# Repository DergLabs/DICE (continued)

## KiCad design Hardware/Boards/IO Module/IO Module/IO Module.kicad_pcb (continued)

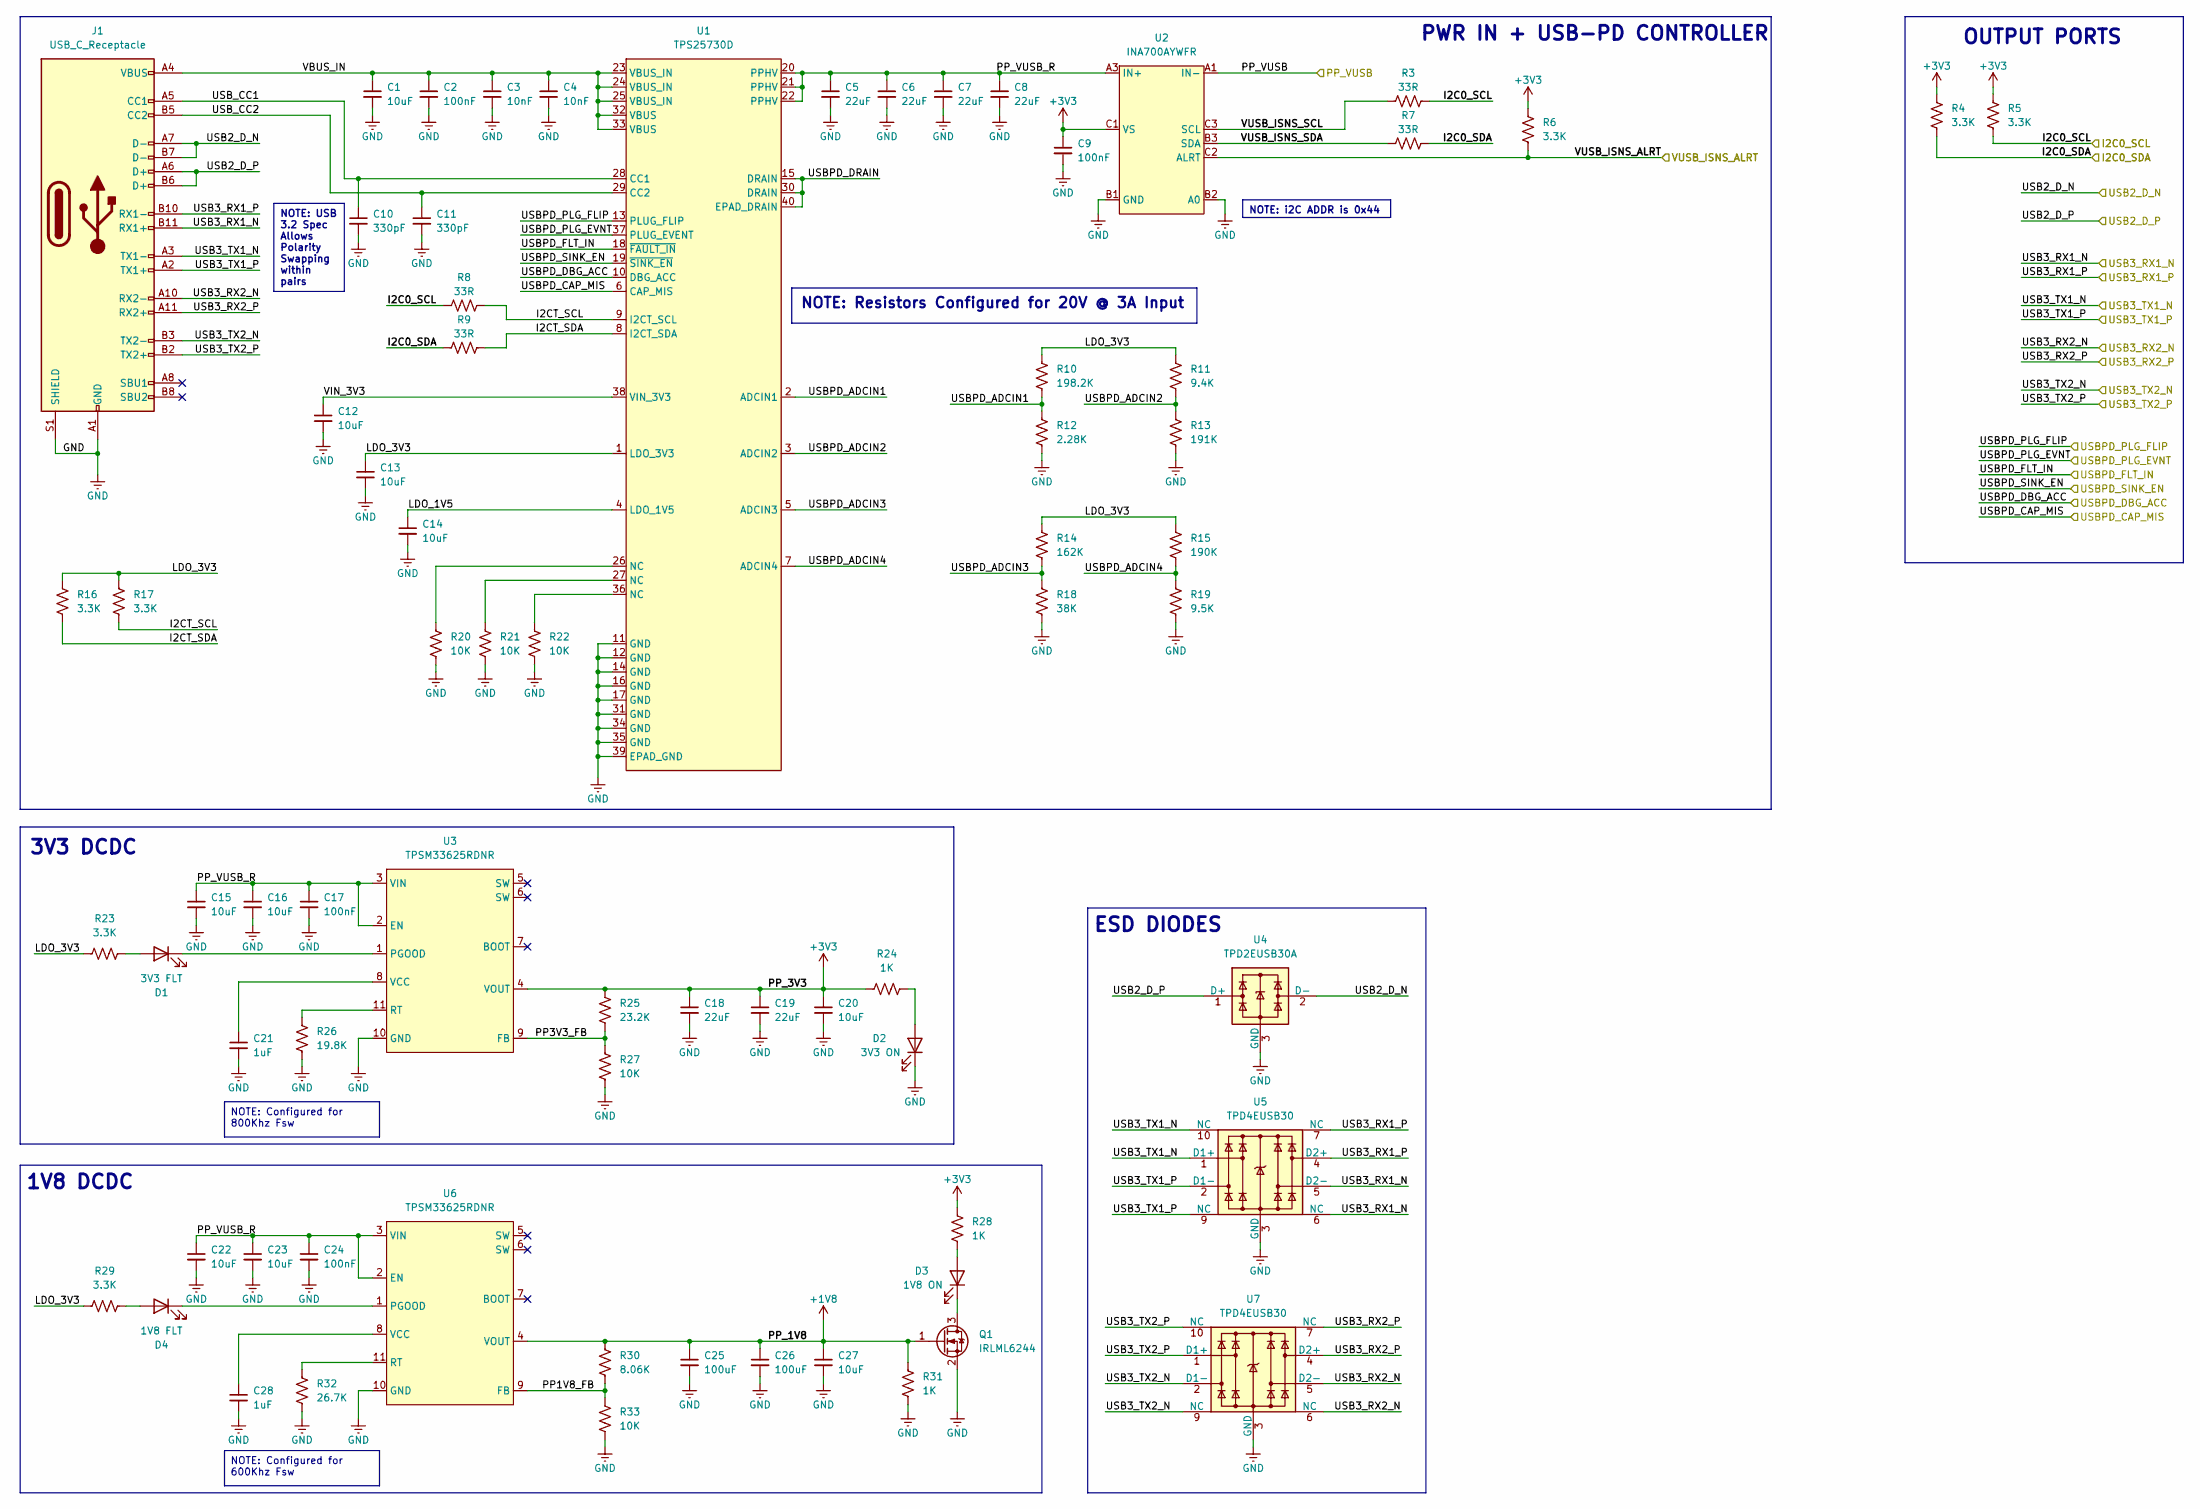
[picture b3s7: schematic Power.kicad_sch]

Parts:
C1, C12, C13, C14, C15, C16, C20, C22, C23, C27: 10uF; C_0603_1608Metric
C2, C9, C17, C24: 100nF; C_0201_0603Metric
C3, C4: 10nF; C_0201_0603Metric
C5, C6, C7, C8, C18, C19: 22uF; C_0805_2012Metric
C10, C11: 330pF; C_0201_0603Metric
C21, C28: 1uF; C_0201_0603Metric
C25, C26: 100uF; C_0805_2012Metric
D1: 3V3 FLT; LED_0603_1608Metric
D2: 3V3 ON; LED_0603_1608Metric
D3: 1V8 ON; LED_0603_1608Metric
D4: 1V8 FLT; LED_0603_1608Metric
J1: USB_C_Receptacle; GCT_USB4056-03-A_REVA2
Q1: IRLML6244; SOT-23
R3, R7, R8, R9: 33R; R_0201_0603Metric
R4, R5, R6, R16, R17, R23, R29: 3.3K; R_0201_0603Metric
R10: 198.2K; R_0201_0603Metric
R11: 9.4K; R_0201_0603Metric
R12: 2.28K; R_0201_0603Metric
R13: 191K; R_0201_0603Metric
R14: 162K; R_0201_0603Metric
R15: 190K; R_0201_0603Metric
R18: 38K; R_0201_0603Metric
R19: 9.5K; R_0201_0603Metric
R20, R21, R22, R27, R33: 10K; R_0201_0603Metric
R24, R28, R31: 1K; R_0201_0603Metric
R25: 23.2K; R_0201_0603Metric
R26: 19.8K; R_0201_0603Metric
R30: 8.06K; R_0201_0603Metric
R32: 26.7K; R_0201_0603Metric
U1: TPS25730D; TPS25730DREFR
U2: INA700AYWFR; INA700_AYWFR
U3, U6: TPSM33625RDNR; RDN0011A-MFG
U4: TPD2EUSB30A; Texas_DRT-3
U5, U7: TPD4EUSB30; USON-10_2.5x1.0mm_P0.5mm

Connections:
+1V8: C25.1, C26.1, C27.1, Q1.1 (G), R30.2, R31.2, U6.4 (VOUT); also elsewhere on the board
+3V3: C9.1, C18.1, C19.1, C20.1, R4.2, R5.2, R6.2, R24.1, R25.2, R28.2, U2.C1 (VS), U3.4 (VOUT); also elsewhere on the board
/Top/MCU/I2C0_SCL: R3.1, R5.1, R8.2; also elsewhere on the board
/Top/MCU/I2C0_SDA: R4.1, R7.1, R9.2; also elsewhere on the board
/Top/MCU/USBPD_CAP_MIS: U1.6 (CAP_MIS); also elsewhere on the board
/Top/MCU/USBPD_DBG_ACC: U1.10 (DBG_ACC); also elsewhere on the board
/Top/MCU/USBPD_FLT_IN: U1.18 (~FAULT_IN); also elsewhere on the board
/Top/MCU/USBPD_PLG_EVNT: U1.37 (PLUG_EVENT); also elsewhere on the board
/Top/MCU/USBPD_PLG_FLIP: U1.13 (PLUG_FLIP); also elsewhere on the board
/Top/MCU/USBPD_SINK_EN: U1.19 (~SINK_EN); also elsewhere on the board
/Top/MCU/VUSB_ISNS_ALRT: R6.1, U2.C2 (ALRT); also elsewhere on the board
/Top/PP_VUSB: U2.A1 (IN-); also elsewhere on the board
/Top/Power/I2CT_SCL: R8.1, R17.1, U1.9 (I2CT_SCL)
/Top/Power/I2CT_SDA: R9.1, R16.1, U1.8 (I2CT_SDA)
/Top/Power/LDO_1V5: C14.1, U1.4 (LDO_1V5)
/Top/Power/LDO_3V3: C13.1, R10.2, R11.2, R14.2, R15.2, R16.2, R17.2, R23.1, R29.1, U1.1 (LDO_3V3)
/Top/Power/PP1V8_FB: R30.1, R33.2, U6.9 (FB)
/Top/Power/PP3V3_FB: R25.1, R27.2, U3.9 (FB)
/Top/Power/PP_VUSB_R: C5.1, C6.1, C7.1, C8.1, C15.1, C16.1, C17.1, C22.1, C23.1, C24.1, U1.20 (PPHV), U1.21 (PPHV), U1.22 (PPHV), U2.A3 (IN+), U3.2 (EN), U3.3 (VIN), U6.2 (EN), U6.3 (VIN)
/Top/Power/USB2_D_N: J1.A7 (D-), J1.B7 (D-), U4.2 (D-); also elsewhere on the board
/Top/Power/USB2_D_P: J1.A6 (D+), J1.B6 (D+), U4.1 (D+); also elsewhere on the board
/Top/Power/USB3_RX1_N: J1.B11 (RX1+), U5.5 (D2-), U5.6 (NC); also elsewhere on the board
/Top/Power/USB3_RX1_P: J1.B10 (RX1-), U5.4 (D2+), U5.7 (NC); also elsewhere on the board
/Top/Power/USB3_RX2_N: J1.A10 (RX2-), U7.5 (D2-), U7.6 (NC); also elsewhere on the board
/Top/Power/USB3_RX2_P: J1.A11 (RX2+), U7.4 (D2+), U7.7 (NC); also elsewhere on the board
/Top/Power/USB3_TX1_N: J1.A3 (TX1-), U5.1 (D1+), U5.10 (NC); also elsewhere on the board
/Top/Power/USB3_TX1_P: J1.A2 (TX1+), U5.2 (D1-), U5.9 (NC); also elsewhere on the board
/Top/Power/USB3_TX2_N: J1.B3 (TX2-), U7.2 (D1-), U7.9 (NC); also elsewhere on the board
/Top/Power/USB3_TX2_P: J1.B2 (TX2+), U7.1 (D1+), U7.10 (NC); also elsewhere on the board
/Top/Power/USBPD_ADCIN1: R10.1, R12.2, U1.2 (ADCIN1)
/Top/Power/USBPD_ADCIN2: R11.1, R13.2, U1.3 (ADCIN2)
/Top/Power/USBPD_ADCIN3: R14.1, R18.2, U1.5 (ADCIN3)
/Top/Power/USBPD_ADCIN4: R15.1, R19.2, U1.7 (ADCIN4)
/Top/Power/USBPD_DRAIN: U1.15 (DRAIN), U1.30 (DRAIN), U1.40 (EPAD_DRAIN)
/Top/Power/USB_CC1: C10.1, J1.A5 (CC1), U1.28 (CC1)
/Top/Power/USB_CC2: C11.1, J1.B5 (CC2), U1.29 (CC2)
/Top/Power/VBUS_IN: C1.1, C2.1, C3.1, C4.1, J1.A4 (VBUS), J1.A9 (VBUS), J1.B4 (VBUS), J1.B9 (VBUS), U1.23 (VBUS_IN), U1.24 (VBUS_IN), U1.25 (VBUS_IN), U1.32 (VBUS), U1.33 (VBUS)
/Top/Power/VIN_3V3: C12.1, U1.38 (VIN_3V3)
/Top/Power/VUSB_ISNS_SCL: R3.2, U2.C3 (SCL)
/Top/Power/VUSB_ISNS_SDA: R7.2, U2.B3 (SDA)
GND: C1.2, C2.2, C3.2, C4.2, C5.2, C6.2, C7.2, C8.2, C9.2, C10.2, C11.2, C12.2, C13.2, C14.2, C15.2, C16.2, C17.2, C18.2, C19.2, C20.2, C21.2, C22.2, C23.2, C24.2, C25.2, C26.2, C27.2, C28.2, D2.1 (K), J1.A1 (GND), J1.A12 (GND), J1.B1 (GND), J1.B12 (GND), J1.S1 (SHIELD), Q1.2 (S), R12.1, R13.1, R18.1, R19.1, R20.1, R21.1, R22.1, R26.1, R27.1, R31.1, R32.1, R33.1, U1.11 (GND), U1.12 (GND), U1.14 (GND), U1.16 (GND), U1.17 (GND), U1.31 (GND), U1.34 (GND), U1.35 (GND), U1.39 (EPAD_GND), U2.B1 (GND), U2.B2 (A0), U3.10 (GND), U4.3 (GND), U5.3 (GND), U5.8 (GND), U6.10 (GND), U7.3 (GND), U7.8 (GND); also elsewhere on the board
unnamed: D1.2 (A), R23.2
unnamed: D1.1 (K), U3.1 (PGOOD)
unnamed: D2.2 (A), R24.2
unnamed: D3.2 (A), R28.1
unnamed: D3.1 (K), Q1.3 (D)
unnamed: D4.2 (A), R29.2
unnamed: D4.1 (K), U6.1 (PGOOD)
unnamed: R20.2, U1.26 (NC)
unnamed: R21.2, U1.27 (NC)
unnamed: R22.2, U1.36 (NC)
unnamed: R26.2, U3.11 (RT)
unnamed: C21.1, U3.8 (VCC)
unnamed: R32.2, U6.11 (RT)
unnamed: C28.1, U6.8 (VCC)

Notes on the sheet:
NOTE: Configured for 800Khz Fsw
NOTE: Resistors Configured for 20V @ 3A Input
NOTE: Configured for 600Khz Fsw
NOTE: USB 3.2 Spec Allows Polarity Swapping within pairs
NOTE: i2C ADDR is 0x44
PWR IN + USB-PD CONTROLLER
OUTPUT PORTS
1V8 DCDC
3V3 DCDC
ESD DIODES

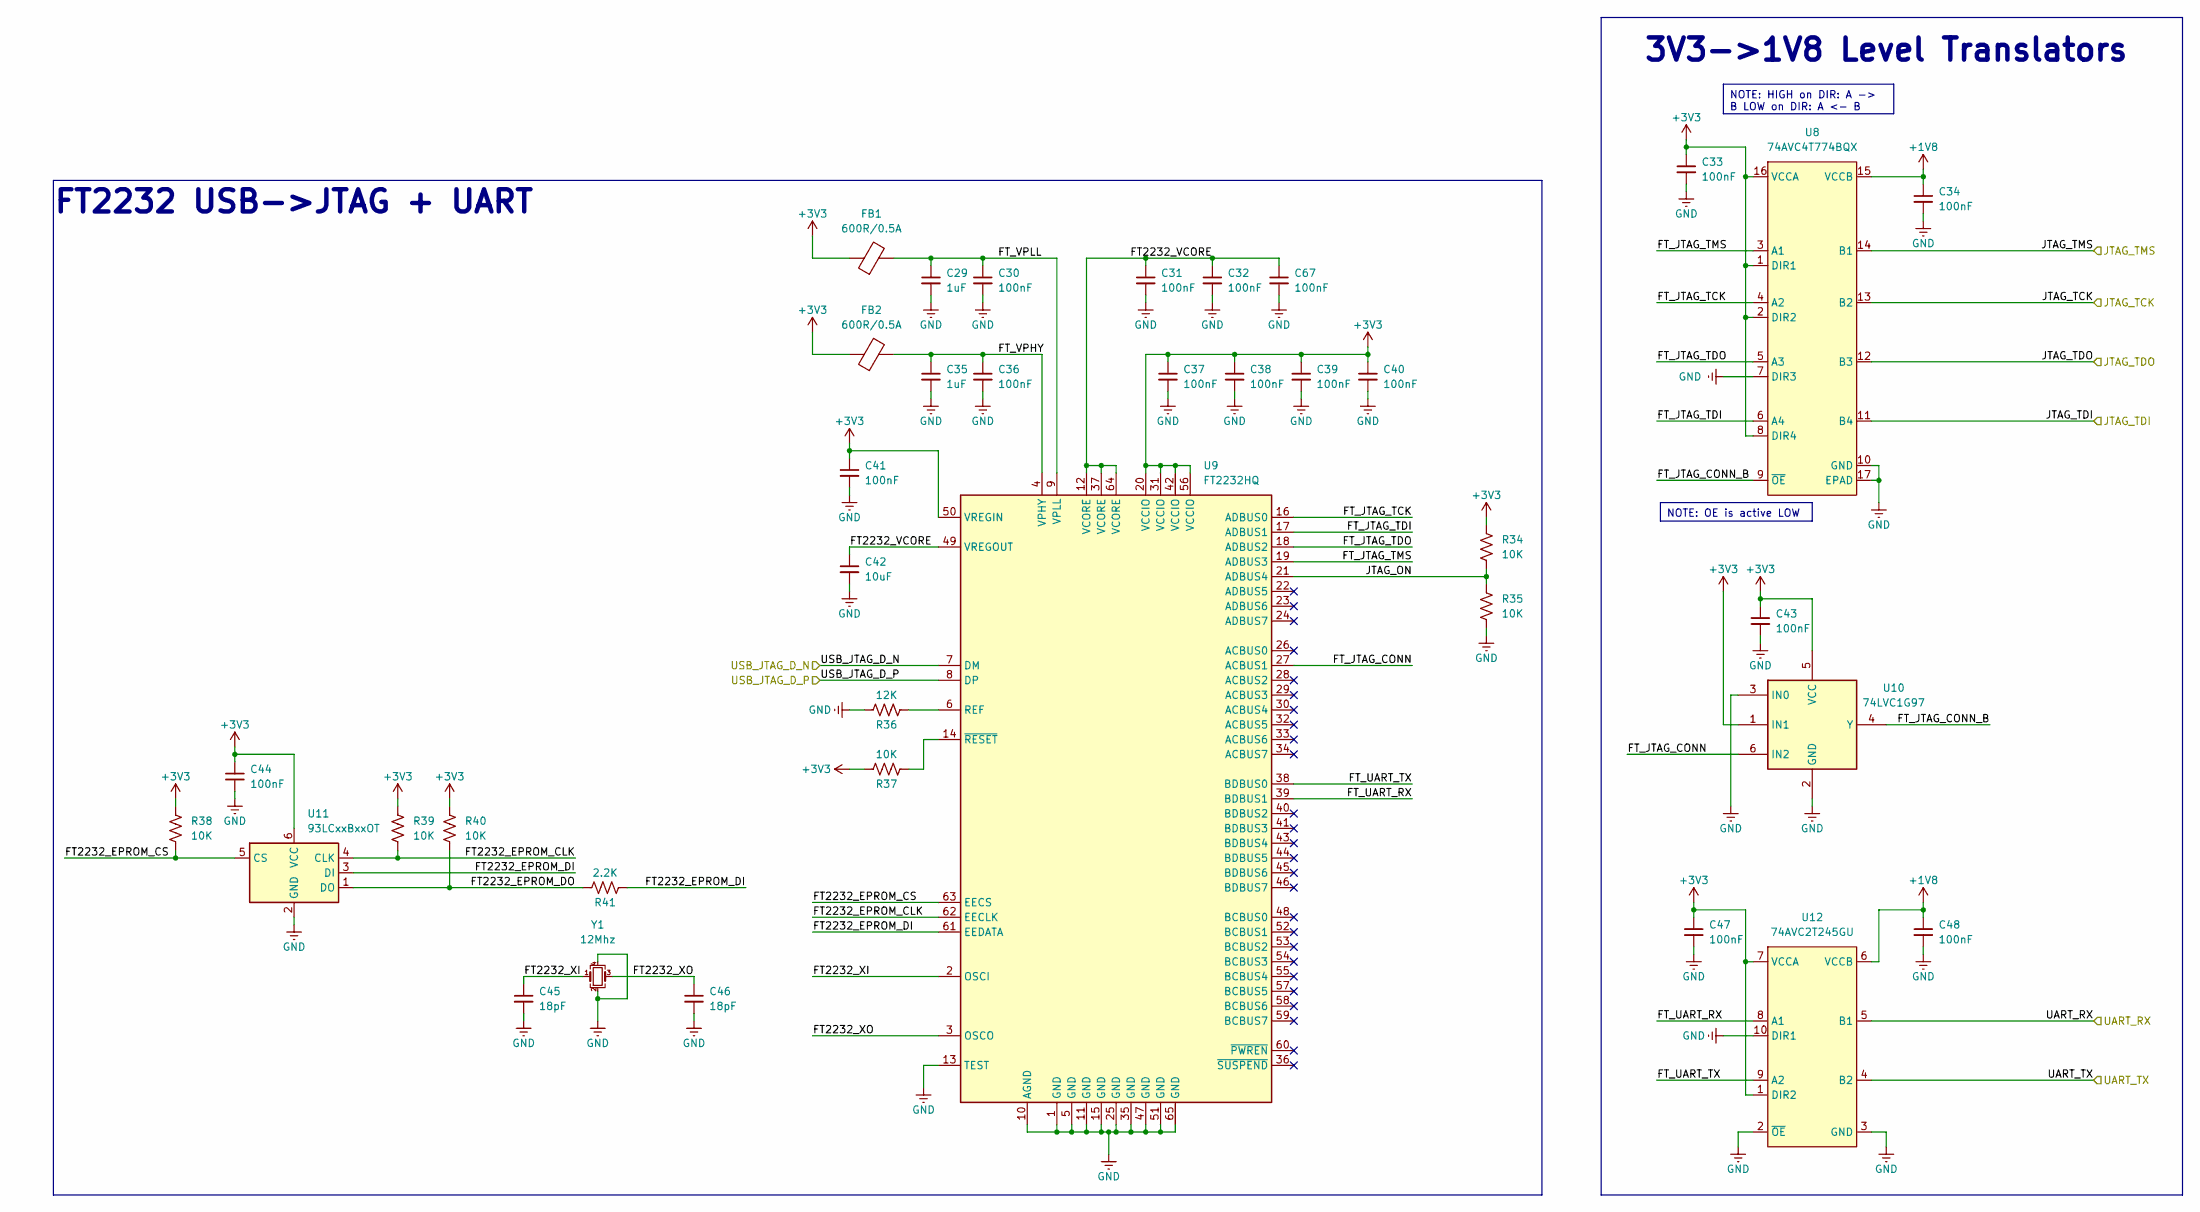
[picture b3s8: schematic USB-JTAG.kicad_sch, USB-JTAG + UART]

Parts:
C29, C35: 1uF; C_0201_0603Metric
C30, C31, C32, C33, C34, C36, C37, C38, C39, C40, C41, C43, C44, C47, C48, C67: 100nF; C_0201_0603Metric
C42: 10uF; C_0603_1608Metric
C45, C46: 18pF; C_0201_0603Metric
FB1, FB2: 600R/0.5A; L_0603_1608Metric
R34, R35, R37, R38, R39, R40: 10K; R_0201_0603Metric
R36: 12K; R_0201_0603Metric
R41: 2.2K; R_0201_0603Metric
U8: 74AVC4T774BQX
U9: FT2232HQ; QFN-64-1EP_9x9mm_P0.5mm_EP4.35x4.35mm
U10: 74LVC1G97; SOT-563
U11: 93LCxxBxxOT; SOT-23-6
U12: 74AVC2T245GU
Y1: 12Mhz; Oscillator_SMD_Abracon_ASE-4Pin_3.2x2.5mm

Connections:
+1V8: C34.1, C48.1, U8.15 (VCCB), U12.6 (VCCB); also elsewhere on the board
+3V3: C33.1, C37.1, C38.1, C39.1, C40.1, C41.1, C43.1, C44.1, C47.1, FB1.1, FB2.1, R34.2, R37.2, R38.2, R39.2, R40.2, U8.1 (DIR1), U8.2 (DIR2), U8.8 (DIR4), U8.16 (VCCA), U9.20 (VCCIO), U9.31 (VCCIO), U9.42 (VCCIO), U9.50 (VREGIN), U9.56 (VCCIO), U10.1 (IN1), U10.5 (VCC), U11.6 (VCC), U12.1 (DIR2), U12.7 (VCCA); also elsewhere on the board
/Top/B2B/JTAG_TCK: U8.13 (B2); also elsewhere on the board
/Top/B2B/JTAG_TDI: U8.11 (B4); also elsewhere on the board
/Top/B2B/JTAG_TDO: U8.12 (B3); also elsewhere on the board
/Top/B2B/JTAG_TMS: U8.14 (B1); also elsewhere on the board
/Top/B2B/UART_RX: U12.5 (B1); also elsewhere on the board
/Top/B2B/UART_TX: U12.4 (B2); also elsewhere on the board
/Top/USB Hub/USB_JTAG_D_N: U9.7 (DM); also elsewhere on the board
/Top/USB Hub/USB_JTAG_D_P: U9.8 (DP); also elsewhere on the board
/Top/USB-JTAG/FT2232_EPROM_CLK: R39.1, U9.62 (EECLK), U11.4 (CLK)
/Top/USB-JTAG/FT2232_EPROM_CS: R38.1, U9.63 (EECS), U11.5 (CS)
/Top/USB-JTAG/FT2232_EPROM_DI: R41.1, U9.61 (EEDATA), U11.3 (DI)
/Top/USB-JTAG/FT2232_EPROM_DO: R40.1, R41.2, U11.1 (DO)
/Top/USB-JTAG/FT2232_VCORE: C31.1, C32.1, C42.1, C67.1, U9.12 (VCORE), U9.37 (VCORE), U9.49 (VREGOUT), U9.64 (VCORE)
/Top/USB-JTAG/FT2232_XI: C45.1, U9.2 (OSCI), Y1.1
/Top/USB-JTAG/FT2232_XO: C46.1, U9.3 (OSCO), Y1.3
/Top/USB-JTAG/FT_JTAG_CONN: U9.27 (ACBUS1), U10.6 (IN2)
/Top/USB-JTAG/FT_JTAG_CONN_B: U8.9 (~OE), U10.4 (Y)
/Top/USB-JTAG/FT_JTAG_TCK: U8.4 (A2), U9.16 (ADBUS0)
/Top/USB-JTAG/FT_JTAG_TDI: U8.6 (A4), U9.17 (ADBUS1)
/Top/USB-JTAG/FT_JTAG_TDO: U8.5 (A3), U9.18 (ADBUS2)
/Top/USB-JTAG/FT_JTAG_TMS: U8.3 (A1), U9.19 (ADBUS3)
/Top/USB-JTAG/FT_UART_RX: U9.39 (BDBUS1), U12.8 (A1)
/Top/USB-JTAG/FT_UART_TX: U9.38 (BDBUS0), U12.9 (A2)
/Top/USB-JTAG/FT_VPHY: C35.1, C36.1, FB2.2, U9.4 (VPHY)
/Top/USB-JTAG/FT_VPLL: C29.1, C30.1, FB1.2, U9.9 (VPLL)
/Top/USB-JTAG/JTAG_ON: R34.1, R35.2, U9.21 (ADBUS4)
GND: C29.2, C30.2, C31.2, C32.2, C33.2, C34.2, C35.2, C36.2, C37.2, C38.2, C39.2, C40.2, C41.2, C42.2, C43.2, C44.2, C45.2, C46.2, C47.2, C48.2, C67.2, R35.1, R36.2, U8.7 (DIR3), U8.10 (GND), U8.17 (EPAD), U9.1 (GND), U9.5 (GND), U9.10 (AGND), U9.11 (GND), U9.13 (TEST), U9.15 (GND), U9.25 (GND), U9.35 (GND), U9.47 (GND), U9.51 (GND), U9.65 (GND), U10.2 (GND), U10.3 (IN0), U11.2 (GND), U12.2 (~OE), U12.3 (GND), U12.10 (DIR1), Y1.2, Y1.4; also elsewhere on the board
unnamed: R36.1, U9.6 (REF)
unnamed: R37.1, U9.14 (~RESET)

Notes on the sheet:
NOTE: OE is active LOW
NOTE: HIGH on DIR: A -> B LOW on DIR: A <- B
FT2232 USB->JTAG + UART
3V3->1V8 Level Translators

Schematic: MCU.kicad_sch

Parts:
C50, C69, C70, C71, C72, C74, C75, C76: 100nF; C_0201_0603Metric
C68, C73: 1uF; C_0201_0603Metric
C77, C78: 18pF; C_0201_0603Metric
D5: MCU Heartbeat; LED_0603_1608Metric
R47: 10K; R_0201_0603Metric; MPN RC0402JR-0710KL
R48: 1K; R_0201_0603Metric
SW1: RST; SW_Push_SPST_NO_Alps_SKRK
TP5, TP6: TestPoint; TestPoint_Pad_D1.0mm
U14: W25Q16JVUXIQ TR; USON-8_UX_2x3x0p6_WIN
U15: RP2040; QFN-56-1EP_7x7mm_P0.4mm_EP3.2x3.2mm
Y3: 12Mhz; Oscillator_SMD_Abracon_ASE-4Pin_3.2x2.5mm

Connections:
+3V3: C70.1, C71.1, C72.1, C73.1, C74.1, C75.1, C76.1, U14.8 (VCC), U15.1 (IOVDD), U15.10 (IOVDD), U15.22 (IOVDD), U15.33 (IOVDD), U15.42 (IOVDD), U15.43 (ADC_AVDD), U15.44 (VREG_IN), U15.48 (USB_VDD), U15.49 (IOVDD); also elsewhere on the board
/Top/B2B/CAM_LED_EN: U15.5 (GPIO3); also elsewhere on the board
/Top/B2B/CAM_PWR_EN: U15.4 (GPIO2); also elsewhere on the board
/Top/B2B/MBUS_D0: U15.11 (GPIO8); also elsewhere on the board
/Top/B2B/MBUS_D1: U15.12 (GPIO9); also elsewhere on the board
/Top/B2B/MBUS_D2: U15.13 (GPIO10); also elsewhere on the board
/Top/B2B/MBUS_D3: U15.14 (GPIO11); also elsewhere on the board
/Top/B2B/MBUS_D4: U15.15 (GPIO12); also elsewhere on the board
/Top/B2B/MBUS_D5: U15.16 (GPIO13); also elsewhere on the board
/Top/B2B/MBUS_D6: U15.17 (GPIO14); also elsewhere on the board
/Top/B2B/MBUS_D7: U15.18 (GPIO15); also elsewhere on the board
/Top/B2B/MBUS_D8: U15.27 (GPIO16); also elsewhere on the board
/Top/B2B/MBUS_D9: U15.28 (GPIO17); also elsewhere on the board
/Top/B2B/MBUS_D10: U15.29 (GPIO18); also elsewhere on the board
/Top/B2B/MBUS_D11: U15.30 (GPIO19); also elsewhere on the board
/Top/B2B/MBUS_D12: U15.31 (GPIO20); also elsewhere on the board
/Top/B2B/MBUS_D13: U15.32 (GPIO21); also elsewhere on the board
/Top/B2B/MBUS_D14: U15.34 (GPIO22); also elsewhere on the board
/Top/B2B/MBUS_D15: U15.35 (GPIO23); also elsewhere on the board
/Top/Camera FPC/I2C1_SCL: U15.9 (GPIO7); also elsewhere on the board
/Top/Camera FPC/I2C1_SDA: U15.8 (GPIO6); also elsewhere on the board
/Top/MCU/I2C0_SCL: U15.7 (GPIO5); also elsewhere on the board
/Top/MCU/I2C0_SDA: U15.6 (GPIO4); also elsewhere on the board
/Top/MCU/MCU_HB_LED: R48.1, U15.37 (GPIO25)
/Top/MCU/MCU_XI: C77.1, U15.20 (XIN), Y3.1
/Top/MCU/MCU_XO: C78.1, U15.21 (XOUT), Y3.3
/Top/MCU/QSPI_CLK: U14.6 (CLK), U15.52 (QSPI_SCLK)
/Top/MCU/QSPI_CS: R47.1, U14.1 (/CS), U15.56 (QSPI_SS)
/Top/MCU/QSPI_D0: U14.5 (DI(IO0)), U15.53 (QSPI_SD0)
/Top/MCU/QSPI_D1: U14.2 (DO(IO1)), U15.55 (QSPI_SD1)
/Top/MCU/QSPI_D2: U14.3 (/WP(IO2)), U15.54 (QSPI_SD2)
/Top/MCU/QSPI_D3: U14.7 (/HLD/RST(IO3)), U15.51 (QSPI_SD3)
/Top/MCU/USBPD_CAP_MIS: U15.40 (GPIO28_ADC2); also elsewhere on the board
/Top/MCU/USBPD_DBG_ACC: U15.39 (GPIO27_ADC1); also elsewhere on the board
/Top/MCU/USBPD_FLT_IN: U15.36 (GPIO24); also elsewhere on the board
/Top/MCU/USBPD_PLG_EVNT: U15.3 (GPIO1); also elsewhere on the board
/Top/MCU/USBPD_PLG_FLIP: U15.2 (GPIO0); also elsewhere on the board
/Top/MCU/USBPD_SINK_EN: U15.38 (GPIO26_ADC0); also elsewhere on the board
/Top/MCU/USB_MCU_D_N: U15.46 (USB_DM); also elsewhere on the board
/Top/MCU/USB_MCU_D_P: U15.47 (USB_DP); also elsewhere on the board
/Top/MCU/VMCU_1V1: C50.1, C68.1, C69.1, U15.23 (DVDD), U15.45 (VREG_VOUT), U15.50 (DVDD)
/Top/MCU/VUSB_ISNS_ALRT: U15.41 (GPIO29_ADC3); also elsewhere on the board
GND: C50.2, C68.2, C69.2, C70.2, C71.2, C72.2, C73.2, C74.2, C75.2, C76.2, C77.2, C78.2, D5.1 (K), SW1.1 (A), U14.4 (GND), U14.9 (EPAD), U15.19 (TESTEN), U15.57 (GND), Y3.2, Y3.4; also elsewhere on the board
unnamed: D5.2 (A), R48.2
unnamed: R47.2, SW1.2 (B)
unnamed: TP5.1, U15.24 (SWCLK)
unnamed: TP6.1, U15.25 (SWD)

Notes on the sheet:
System Controller MCU

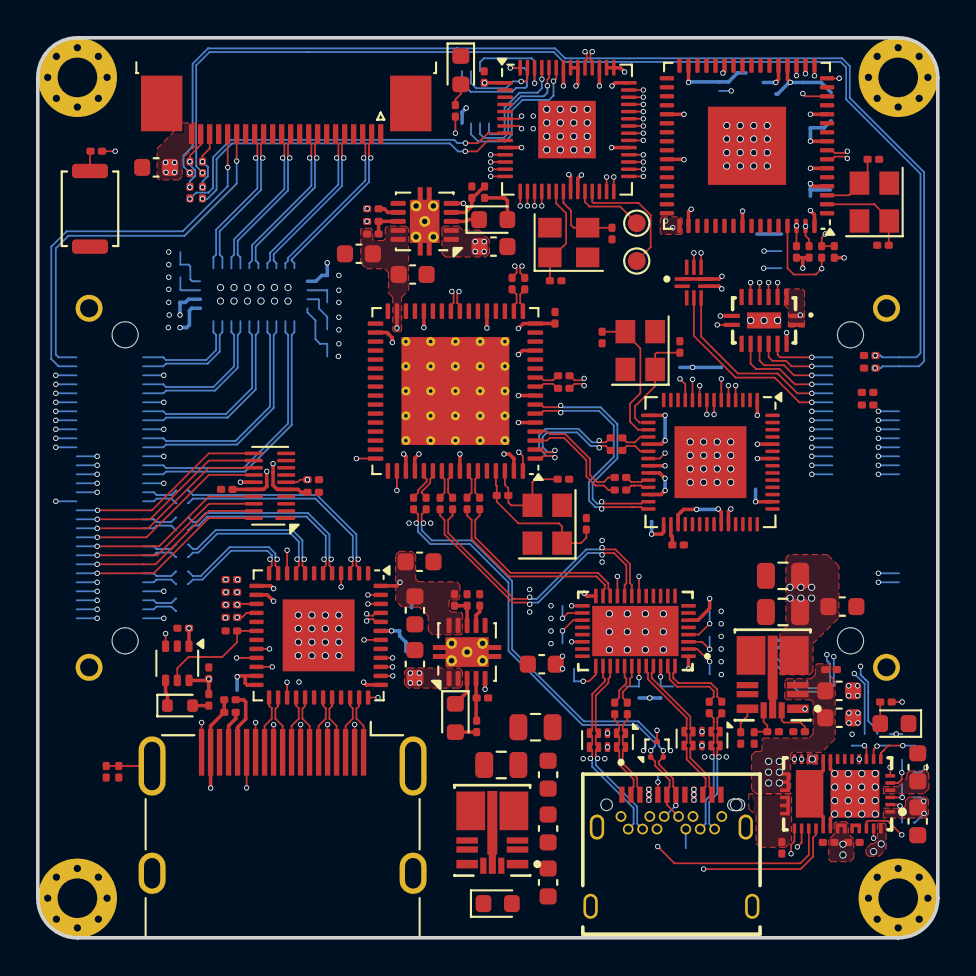
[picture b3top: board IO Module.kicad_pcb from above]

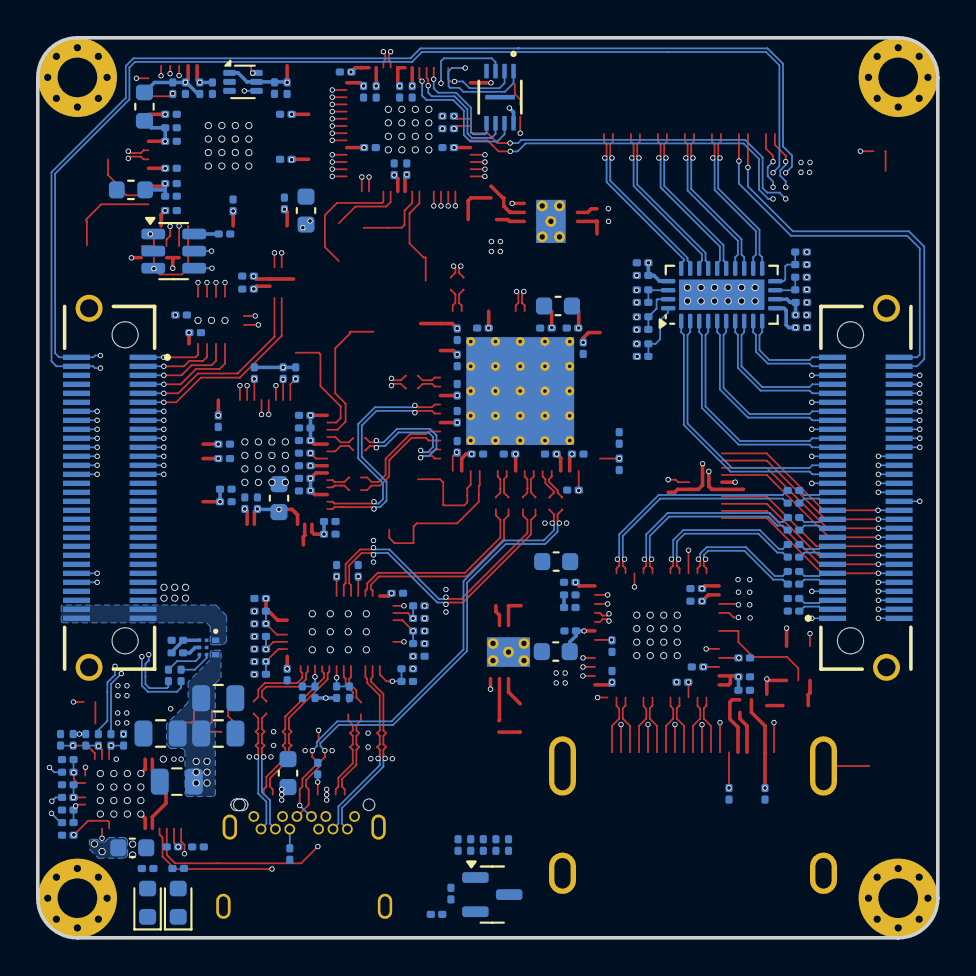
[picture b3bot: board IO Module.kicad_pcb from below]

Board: 8 copper layers, 50.0 x 50.0 mm, 319 parts (183 on the bottom side), 299 nets.

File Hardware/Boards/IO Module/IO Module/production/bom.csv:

Designator,Footprint,Quantity,Value,LCSC Part #
"C1, C109, C114, C115, C116, C118, C12, C124, C13, C14, C148, C15, C16, C20, C22, C23, C27, C42, C49, C80, C81, C82, C84",0603,23,10uF,
"C10, C11",0201,2,330pF,
"C100, C113, C119, C120, C121, C122, C123, C125, C126, C127, C128, C130, C131, C132, C133, C134, C135, C136, C137, C138, C140, C143, C144, C145, C149, C150, C151, C152, C154, C155, C156, C17, C2, C24, C30, C31, C32, C33, C34, C36, C37, C38, C39, C40, C41, C43, C44, C47, C48, C50, C51, C52, C53, C54, C55, C56, C57, C58, C61, C62, C63, C64, C67, C69, C70, C71, C72, C74, C75, C76, C85, C86, C87, C88, C89, C9, C90, C91, C92, C93, C96, C97, C98, C99",0201,84,100nF,
"C101, C102, C103, C105, C106, C107, C108, C94",0201,8,220nF,
"C104, C112, C153, C21, C28, C29, C35, C59, C60, C68, C73, C79, C95",0201,13,1uF,
"C110, C111, C45, C46, C65, C66, C77, C78",0201,8,18pF,
"C117, C129, C146, C147, C3, C4, C83",0201,7,10nF,
"C18, C19, C5, C6, C7, C8",0805,6,22uF,
"C25, C26",0805,2,100uF,
D1,0603,1,3V3 FLT,
D2,0603,1,3V3 ON,
D3,0603,1,1V8 ON,
D4,0603,1,1V8 FLT,
D5,0603,1,MCU Heartbeat,
"D6, D7",0603,2,1V1 FLT,
"FB1, FB2",0603,2,600R/0.5A,
J1,GCT_USB4056-03-A_REVA2,1,USB_C_Receptacle,
"J2, J3",SAMTEC_LSHM-130-XX.X-XXX-DV-A-S-K-XX,2,LSHM-130-XX.X-XXX-DV-A-S-K-XX,
J4,HDMI_A_Molex_208658-1001_Horizontal,1,HDMI_A,
J5,TE_2-1734839-2_1x22-1MP_P0.5mm_Horizontal,1,Cam FPC,
Q1,SOT-23,1,IRLML6244,
"R1, R16, R17, R2, R23, R29, R4, R5, R51, R6, R72",0201,11,3.3K,
R10,0201,1,198.2K,
"R100, R101, R102, R3, R34, R52, R53, R55, R57, R58, R59, R61, R63, R67, R68, R7, R8, R83, R84, R85, R86, R9, R99",0201,23,33R,
R103,0201,1,1.6K,
"R104, R105, R106, R107, R108, R109, R110, R111, R112, R113, R114, R115, R116, R117, R24, R28, R31, R35, R45, R48, R64, R65, R66, R69, R75, R79, R81",0201,27,1K,
R11,0201,1,9.4K,
R12,0201,1,2.28K,
R13,0201,1,191K,
R14,0201,1,162K,
R15,0201,1,190K,
R18,0201,1,38K,
R19,0201,1,9.5K,
"R20, R21, R22, R27, R33, R37, R38, R39, R40, R43, R44, R46, R50, R71, R91, R92, R93, R94, R95, R96, R97, R98",0201,22,10K,
R25,0201,1,23.2K,
R26,0201,1,19.8K,
R30,0201,1,8.06K,
R32,0201,1,26.7K,
R36,0201,1,12K,
"R41, R73, R74",0201,3,2.2K,
R42,0201,1,5.1K,
R47,0201,1,10K,RC0402JR-0710KL
"R49, R70",0201,2,3.74K,
R54,0201,1,44.2K,
R56,0201,1,1.13K,
R60,0201,1,9.53K,
"R62, R76",0201,2,1M,
"R77, R78, R80",0201,3,100K,
R87,0201,1,7K,
"R89, R90",0201,2,4.7K,
SW1,SW_Push_SPST_NO_Alps_SKRK,1,RST,
"TP1, TP2, TP3, TP4",MountingHole_2.2mm_M2_Pad_Via,4,MH,
"TP5, TP6",TestPoint_Pad_D1.0mm,2,TestPoint,
U1,TPS25730DREFR,1,TPS25730D,
"U10, U17, U25, U26",USON-10_2.5x1.0mm_P0.5mm,4,TPD4E02B04DQA,
U11,SOT-23-6,1,93LCxxBxxOT,
U12,74AVC2T245GU,1,74AVC2T245GU,
U13,QFN-56-1EP_7x7mm_P0.4mm_EP4x4mm,1,FT600Q,
U14,USON-8_UX_2x3x0p6_WIN,1,W25Q16JVUXIQ TR,
U15,QFN-56-1EP_7x7mm_P0.4mm_EP3.2x3.2mm,1,RP2040,
"U16, U19",VSON-10-1EP_3x3mm_P0.5mm_EP1.65x2.4mm_ThermalVias,2,TPS74801AWDRC,
U18,QFN-64-1EP_9x9mm_P0.5mm_EP6x6mm_ThermalVias,1,TUSB8041,
U2,INA700_AYWFR,1,INA700AYWFR,
U20,HWSON8_SOT1069-2_NXP,1,PCA9517ATP,
U21,USON-20_2x4mm_P0.4mm,1,TXB0108DQSR,
U23,QFN-28-1EP_3x6mm_P0.5mm_EP1.7x4.75mm,1,SN65DPHY440SS,
U24,WQFN_142RNQT_TEX,1,TUSB1142,
U27,SOT-89-3,1,L78L05_SOT89,
"U3, U6",RDN0011A-MFG,2,TPSM33625RDNR,
U4,Texas_DRT-3,1,TPD2EUSB30A,
U5,QFN-40-1EP_5x5mm_P0.4mm_EP3.6x3.6mm,1,SN75DP159RSB,
U7,15DSBGA-TEXAS,1,TPD5S116,
U8,74AVC4T774BQX,1,74AVC4T774BQX,
U9,QFN-64-1EP_9x9mm_P0.5mm_EP4.35x4.35mm,1,FT2232HQ,
"Y1, Y3",Oscillator_SMD_Abracon_ASE-4Pin_3.2x2.5mm,2,12Mhz,
Y2,Oscillator_SMD_Abracon_ASE-4Pin_3.2x2.5mm,1,30Mhz,
Y4,Oscillator_SMD_Abracon_ASE-4Pin_3.2x2.5mm,1,24Mhz,
